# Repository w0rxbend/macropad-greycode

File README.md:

# greycode

A 3 x 3 macropad with a knob and an OLED that changes with the app in front.
FreeCAD in focus: the keys become views, undo and visibility, the OLED shows their names, the edge
light turns orange. A build fails: the edge blinks red and says why.

Keymaps are edited live in [Vial](https://get.vial.today). App profiles, labels, colours and
host actions live in one TOML file that the PC daemon `greyd` reloads on save.

*A render of the case model, not a photo.*

> **Status: design files and software only. Nothing has been built.**
> No board ordered, no case milled, no firmware flashed. Every claim below is what the design files
> and their automatic checks say.

## Status

Checked on 2026-11-15 by running the commands in the last column.

| Part | State | Check |
|---|---|---|
| Firmware | QMK/Vial for RP2040; builds `firmware/dist/greycode_vial.uf2` (vial-qmk `dd43959a`) | `just firmware` |
| Host link (pad side) | 10 native tests pass under ASan + UBSan | `just test-firmware` |
| greyd, greyctl | 45 tests pass, clippy and rustfmt clean. sway backend ran live; Hyprland against fake sockets only; X11 read once on XWayland | `just test-host` |
| FreeCAD add-on | 11 tests against a fake greyd. Not run inside FreeCAD | `just test-freecad` |
| Configurator | Core 32 tests, UI logic 9 tests pass. **Window not built**: needs `webkit2gtk-4.1` | `just test-configurator` |
| PCB | Generated KiCad 9 board, 4 layers, 66 x 96 mm. 892 tracks, 213 vias, 0 unrouted pads. DRC 0 violations, 0 unconnected, 0 parity issues; ERC clean; 8 `board.toml` contract groups match; rebuild byte-repeatable; 48 generator tests | `just pcb`, `just pcb-test` |
| Order files | JLCPCB Gerbers, drill, BOM (22 lines, LCSC numbers), CPL (78 parts); agree with the board. Bottom-side rotations not verified | `just pcb-fab` |
| Case | build123d model, 6061-T6. Self-test 20 of 20; 990 part pairs at rest and 429 pressed, 0 clashes; walls and metal between cuts at least 1.0 mm; inside corners R1.5 wherever the tool reaches over 3 mm; STEP and STL read back clean | `just cad` |
| Pins | 12 checks: firmware and greyd agree with `board.toml` | `just check` |
| Real hardware | **None** | - |

## What it is

| | |
|---|---|
| MCU | RP2040, USB-C |
| Keys | 9 x MX on hot-swap sockets, one GPIO each |
| Knob | EC11 with push. Tap: mute. Hold: FN layer |
| Display | 1.3" 128 x 64 OLED (SH1106, I2C): profile name, the nine key labels, alert text |
| Light | 9 per-key RGB, 6 edge LEDs behind a slot in the case for alerts and the profile colour |
| Firmware | QMK + Vial: 16 layers, encoder map, macros, tap dance, combos, VialRGB |
| Host | `greyd` (Linux: sway, Hyprland, X11), `greyctl`, FreeCAD add-on, configurator |
| Case | Milled 6061-T6 top shell with built-in switch plate and base, knurled knob, frosted light strip in a shadow gap, smoked lens. 77 x 107 x 17.6 mm, 35.0 mm to the knob top. Seven M2 x 10 screws from below |
| PCB | RP2040, W25Q128JVS, USB-C on the underside, 9 hot-swap sockets, 15 SK6812 (9 per key, 6 side-emitting at the front edge), 4 layers |

## Stock keymap

Layer 0 is the base; layers 1-14 are app profiles; 15 is FN (hold the knob).
Edit any of it in Vial; `KC_TRNS` in a profile falls through to the base layer.

| Layer | Keys, row by row | Knob |
|---|---|---|
| 0 Base | Prev Play Next / Copy Paste Undo / HOST0 HOST1 HOST2 | Volume |
| 1 FreeCAD | Iso Front Right / Top Hide Delete / Undo Redo Esc | Zoom |
| 2 KiCad PCB | Route Drag Move / Rotate Via Props / Fill Delete Esc | Zoom (F1/F2) |
| 3 Browser | Reopen New Close / Back URL Forward / Zoom- Zoom0 Zoom+ | Tabs |
| 4 Sketcher | Line Circle Rect / Coincident Horizontal Vertical / Dimension Construction Esc | Zoom |
| 15 FN | RGB on/off, next effect, hue / sat, speed, brightness / -, -, **bootloader** | Brightness |

## Use it

1. **Flash.** Hold BOOT, plug in (or double-tap reset), copy `firmware/dist/greycode_vial.uf2` to the
   `RPI-RP2` drive.
2. **Install greyd** and the udev rule: [host/README.md](host/README.md).
3. **Profiles.** Copy `host/config.example.toml` to `~/.config/greycode/config.toml` and edit it.
4. **Keys.** Open Vial, change a profile's layer. It applies at once.
5. **Alerts.** `greyctl alert error "CI failed" --timeout 60`.
6. **FreeCAD states.** Install the add-on ([freecad/README.md](freecad/README.md)): opening a sketch
   switches the pad to the Sketcher layer.

Before ordering anything, read the open points in [pcb/README.md](pcb/README.md) and
[cad/README.md](cad/README.md), and [docs/architecture.md](docs/architecture.md#open-points).

## Work on it

| Command | Does | Needs |
|---|---|---|
| `just test` | Firmware link, greyd, configurator, FreeCAD add-on, PCB generator, pins (under a minute) | gcc, Rust, Python 3.11+, node |
| `just cad` | Case checks, STEP/STL, renders (about 1 minute) | `cad/.venv` (see `cad/README.md`) |
| `just pcb` | Schematic, placement, routing, DRC, contract, order files | Docker, `kicad/kicad:9.0.9` |
| `just firmware` | Fetch pinned vial-qmk (first run), build the UF2 in the QMK container | Docker |
| `just host-run` | greyd from source with the example config | Rust, sway |

`board.toml` holds pins and parts. Change a pin there, then in `firmware/greycode/`, then run
`just check`.

## Where things are

| Path | What |
|---|---|
| [`board.toml`](board.toml) | Pins and parts; the source the firmware (and later PCB and case) is checked against |
| `firmware/greycode/` | QMK keyboard: `keyboard.json`, `greycode.c` (glue), `hostlink.c` (protocol, no QMK), `keymaps/vial/` |
| `firmware/test/` | Native tests and the protocol vectors shared with greyd |
| [`pcb/`](pcb/README.md) | Board generator (`gen/`), generated KiCad project, JLCPCB files in `fab/` |
| [`cad/`](cad/README.md) | Case model, checks, STEP/STL in `exports/`, machine-shop notes |
| [`configurator/`](configurator/README.md) | Tauri app: `core` (logic), `ui` (HTML/JS), `src-tauri` (shell) |
| [`freecad/`](freecad/README.md) | FreeCAD add-on that reports workbench and Sketcher state to greyd |
| [`host/`](host/README.md) | `greyd` and `greyctl` (Rust), example config, udev rule, systemd unit |
| [`docs/architecture.md`](docs/architecture.md) | How it fits together, failure behaviour, roadmap |
| [`docs/protocol.md`](docs/protocol.md) | Host link wire format |
| `docs/legacy/` | Photos of the hand-wired Pro Micro prototype this replaces |
| `tools/check_pins.py` | Firmware and greyd against `board.toml` |

## License

No license file yet. Until one is added, nobody else has the right to reuse this.

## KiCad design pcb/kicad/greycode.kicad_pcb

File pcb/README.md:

# PCB

The board is generated. Nothing in `pcb/kicad/` is drawn by hand: `make -C pcb place` writes the
schematic, the placed and routed board and the pictures in `docs/images/pcb/` from two inputs,
`board.toml` (outline, holes, positions, GPIOs) and `pcb/gen/circuit.py` (parts and nets). The
generator is adapted from `~/Projects/macropad/pcb`.

**Not built.** No board has been ordered, assembled or powered. Everything below is what the design
files say and what the automatic checks confirm, nothing more.

The part models are block models (`gen/models.py`) with heights typed from memory. They show where
things are and on which face; they are not for measuring.

## Status

Checked on 2026-11-15 with the commands below, KiCad 9.0.9 in Docker.

| Check | Result | Command |
|---|---|---|
| Placement, routing | 96 footprints, 55 nets; 892 tracks, 213 vias, 1330.1 mm; **0 unrouted pads** | `make -C pcb place` |
| Schematic ERC (all severities) | 0 errors, 0 warnings | `make -C pcb place` |
| Schematic netlist vs `circuit.py` | 272 pins match | `make -C pcb place` |
| DRC with schematic parity | 0 violations, 0 unconnected pads, 0 footprint errors | `make -C pcb check` |
| DRC at all severities | only the two accepted findings (J1, J2 differ from their library copy: silkscreen trimmed) | `make -C pcb place` |
| Board vs `board.toml` | 8 groups match: outline, 7 holes with keep-outs, 9 keys, knob, OLED header (pins in `OLED_PINS` order), USB-C (mouth 0.50 mm over), 15 LEDs, 15 GPIOs on their pins and 15 open with no copper | `make -C pcb check` |
| Rebuild repeatable | two `place` runs write byte-identical boards, sha256 `17e881e9...29e0` | `make -C pcb repeat` |
| Order files | 78 machine-placed parts on 22 BOM lines; Gerbers, drill files, BOM and CPL agree with the board | `make -C pcb fab` |
| Plain tests | 48 pass (router 15, schematic writer 19, circuit vs `board.toml` and firmware 11, order files 3) | `make -C pcb test` |
| Real hardware | **None** | - |

## Commands

| Command | Does | Time |
|---|---|---|
| `make -C pcb place` | Schematic, ERC, netlist compare, placement checks, routing, pours, DRC, length checks, contract, pictures. Fails on an unrouted pad after writing `routing.txt`. | about 4 min |
| `make -C pcb check` | `kicad-cli pcb drc --schematic-parity`, fails on any error or unconnected item; then the `board.toml` contract | 30 s |
| `make -C pcb fab` | Gerbers, drill files, `greycode-gerbers.zip`, JLCPCB BOM and CPL into `pcb/fab/`, then a check that they agree with the board | 30 s |
| `make -C pcb test` | Plain Python, no Docker: netlist self-check and the unit tests | 2 s |
| `make -C pcb repeat` | `place` twice, then `cmp` on the two board files | about 8 min |
| `make -C pcb order` | Search a routing order again after moving parts or pins; rewrites `gen/route_order.txt` | about 12 min |

KiCad runs in the pinned container `kicad/kicad:9.0.9` through `pcb/kicad.sh`.

## Circuit

[Schematic PDF](../docs/images/pcb/schematic.pdf), [SVG](../docs/images/pcb/schematic.svg). One A3 sheet,
drawn from `circuit.py` with KiCad's own symbols (RP2040, W25Q128JVS, AP2112K-3.3, USBLC6-2SC6,
SN74LVC1T45DBV, USB-C 16P, EC11). `schematic.check_mcu_pins` holds every RP2040 pin in `circuit.py`
against KiCad's RP2040 symbol.

| Block | Parts |
|---|---|
| MCU | RP2040 (QFN-56, bottom face), W25Q128JVSIQ on QSPI, ABM8-272-T3 12 MHz with 15 pF and 1 k, per "Hardware design with RP2040" |
| MCU supply | 100 nF on each IOVDD, DVDD, USB_VDD and ADC_AVDD pin; 1 uF on VREG_VIN and VREG_VOUT (internal 1.1 V regulator); TESTEN to GND |
| USB | HRO TYPE-C-31-M-12 (bottom face, centred on `usb_x`), 5.1 k on CC1/CC2, USBLC6-2SC6, 27 ohm on D+/D-, nSMD050 500 mA polyfuse, AP2112K-3.3 |
| Buttons | BOOT: QSPI_SS to GND through 1 k. RESET: RUN to GND (RUN's internal pull-up, no external one). Both TS-1187A on the bottom face |
| Keys | 9 MX hot-swap sockets on the bottom face, each between its GPIO and GND, no diodes. Footprint drawn from Kailh CPG151101S11; the BOM orders HanElectricity CPG151101S11-2 (C49352235), see open points |
| Knob | EC11E18244AU at `pcb.knob`: A, B, push to GPIO 12/13/11, C and S2 to GND (internal pull-ups) |
| OLED | 1x4 header GND, VCC (3.3 V), SCL, SDA on GPIO 15/14 (I2C1), 4.7 k pull-ups |
| LEDs | 74LVC1T45 (A at 3.3 V, B at 5 V, DIR high) then 330 ohm, then one chain: 9 x SK6812MINI-E reverse-mounted under the keys, then 6 x SK6812 SIDE-A on the front edge, 100 nF each. Chain order = `keyboard.json` order (checked) |
| Probe pads | SWCLK, SWDIO, GND, 5V, 3V3, 1V1 on the bottom face |

## Board

66 x 96 mm, r 1.5, 1.6 mm, 4 layers, seven M2 holes with 5 mm keep-outs on every copper layer
(rule areas), all from `board.toml`. Every machine-placed part is on the bottom face, so JLCPCB
assembles one side. The encoder and the OLED header are through-hole on the top face, hand-soldered.

| Layer | Use |
|---|---|
| F.Cu | Signals that cross others, ground pour |
| In1.Cu | 5 V plane; 3.3 V island over the strip behind the keys; 1.1 V island under the MCU with a lobe to its capacitors |
| In2.Cu | Ground plane, unbroken |
| B.Cu | All machine-placed parts, most tracks, ground pour |

Drawings: [top](../docs/images/pcb/copper-top.svg), [power](../docs/images/pcb/copper-power.svg),
[ground](../docs/images/pcb/copper-ground.svg), [bottom](../docs/images/pcb/copper-bottom.svg),
assembly [top](../docs/images/pcb/assembly-top.svg), [bottom, mirrored](../docs/images/pcb/assembly-bottom.svg).

Design rules (`layout.py`, written into `kicad/greycode.kicad_pro`): 0.15 mm track and clearance,
0.6/0.3 mm vias, 0.3 mm copper to edge. These are the sibling board's JLCPCB 4-layer values; check
them against JLCPCB's capability page on the day you order.

Routing: `gen/router.py` is a two-layer grid router (no autorouter program). `gen/route.py` runs it
in order: four ground vias in the exposed pad, every MCU supply pin with its capacitor and hand-placed
vias, crystal and ESD ground vias, SWD/RUN escapes, USB and crystal nets, VBUS, flash, one via to the
plane for every other supply pad, LED links inside a key row, MCU signals one escape at a time, the
rest shortest first. `gen/route_order.txt` (found by `make -C pcb order`) moves I2C_SCL, I2C_SDA and
ENC_B to the front.

Routed lengths (`routing.txt`): USB connector to MCU D+ 23.42 mm, D- 21.32 mm; XIN 6.40, XOUT 8.10,
XTAL_DRIVE 3.75 mm; QSPI 4.86 to 15.73 mm. The 15 mm QSPI limit (`route.QSPI_LENGTH_LIMIT`) holds
for every QSPI net but QSPI_SS (15.73 mm), which `route.check_sensitive_lengths` leaves out because
it runs on past the flash to the BOOT button's 1 k resistor.

## Order files (`pcb/fab/`)

`greycode-gerbers.zip` (11 Gerber layers, PTH and NPTH drill files), `bom-jlcpcb.csv` (Comment,
Designator, Footprint, LCSC Part #, Manufacturer, Manufacturer Part #), `cpl-jlcpcb.csv`
(Designator, Mid X, Mid Y, Layer, Rotation; Y negative as JLCPCB's KiCad flow writes it) and
`board-sha256.txt`, the board they were made from. `make -C pcb test` fails if the board changes
after `make -C pcb fab`.

LCSC numbers: the parts shared with `~/Projects/macropad` were checked there on 2026-11-12. RP2040
(C2040), W25Q128JVSIQ (C97521), SK6812MINI-E (C5149201) and 4.7 k 0402 (C25900) were checked
against their JLCPCB part pages on 2026-11-15: part number and package only, not stock or price.

Hand-soldered, not in the BOM: EC11E18244AU (C202365) and the 1x4 header (C2337 strip, only if the
OLED module comes without pins).

## Open points

Nothing below is verified on hardware.

- **Bottom-side rotations in the CPL.** KiCad's rotation is written unchanged for bottom parts, and
  the placement point is the body centre. JLCPCB sometimes wants a correction on bottom parts. Check
  every part in JLCPCB's placement preview before paying, especially U1, U5, the LEDs and J1.
- **SK6812MINI-E footprint.** Pin functions (1 VDD, 2 DOUT, 3 GND, 4 DIN) agree with the OPSCO and
  Mutipower pin tables. Pad size, pad positions, cut-out size and which corner pin 1 lands on when
  the part is mounted upside down are guesses (MEASURE). Also ask JLCPCB whether they place
  reverse-mount MINI-E parts; not confirmed.
- **Part substitutions against the brief.** (1) The brief names Kailh hot-swap sockets; the BOM
  orders HanElectricity CPG151101S11-2 (LCSC C49352235), the part the sibling board uses. The
  footprint is drawn from Kailh's CPG151101S11 drawing; that the HanElectricity part shares its pad
  pattern is a guess from the part number (MEASURE against its datasheet, or swap in Kailh's LCSC
  number before ordering). (2) The brief does not list R9, a 330 ohm resistor between the level
  shifter and the first LED, added because the SK6812 SIDE-A datasheet asks for one in the data line.
  (3) Parts the brief left to me: USB-C HRO TYPE-C-31-M-12, fuse TECHFUSE nSMD050; LCSC stock not
  checked.
- **SK6812 SIDE-A pin order** comes from the sibling's footprint (MEASURE).
- **OLED header.** Pin order GND VCC SCL SDA and the row 1.6 mm inside the module's back edge are
  guesses (`circuit.OLED_PINS`, `OLED_HEADER_INSET`, MEASURE). Modules with VCC and GND swapped exist.
  The contract holds the board's header pins, left to right, against `circuit.OLED_PINS`. The module
  size 35.4 x 33.5 mm is typed into `circuit.OLED_MODULE_SIZE` from a comment in `board.toml`, and the
  contract reuses that copy, so "header at the module's back" is not an independent check until
  `board.toml` gets a `pcb.oled_module_size` key (requested).
- **USB-C on the bottom face**, mouth 0.5 mm past the back edge (`circuit.USB_MOUTH_OVERHANG`; the
  contract measures the fab outline without its line width and prints the same 0.50 mm). The case
  needs to know both; they are not in `board.toml` yet.
- **Buttons on the bottom face** need holes in the case floor: BOOT at board.toml (42.0, 63.6), RESET
  at (8.0, 87.0).
- **LED current.** 15 LEDs at up to about 60 mA each at full white is about 0.9 A; the polyfuse holds
  500 mA. The firmware's `max_brightness` 160/255 still allows about 0.56 A. Nobody has measured it.
- **1.1 V decoupling.** The DVDD and VREG_VOUT capacitors (C8, C9, C10) sit 7 to 12 mm from their
  pins and reach them through the 1.1 V island on In1, not by a track. IOVDD pin 10's capacitor (C2)
  also connects through the plane. The RP2040 guide wants them close; this is the compromise the
  pin-out allowed.
- **Two length checks were loosened after the first full route**, both numbers picked without a
  datasheet: the USB D+/D- mismatch limit from the sibling's 2.0 mm to 3.0 mm (measured 2.09 mm), and
  the MCU-side stub of each 27 ohm resistor from 6 mm to 8 mm (measured 7.16 and 7.53 mm). Full-speed
  USB does not care at these sizes; the reasons are in `route.py`. No USB impedance was calculated.
- **VBUS capacitance.** 2.2 uF plus 16 x 100 nF on 5 V (about 3.8 uF); the 10 uF on 3.3 V sits behind
  the regulator. Not measured at plug-in.
- **Crystal** uses Raspberry Pi's reference values; the oscillator is not measured.
- **Fiducials** are three 1 mm marks on the bottom face; JLCPCB adds its own tooling holes.
- **No teardrops**, thermal reliefs only on through-hole pads.
- **Schematic** is generated and passes ERC; no engineer has reviewed it as a drawing.

## Files

| Path | What |
|---|---|
| `gen/circuit.py` | Every part, its LCSC and manufacturer number, position, rotation and nets. Pure Python |
| `gen/layout.py` | Footprints, outline, planes, keep-outs, design rules, exposed-pad paste windows, placement checks |
| `gen/router.py`, `gen/route.py`, `gen/route_order.txt` | Grid router, routing plan, routing order |
| `gen/schematic.py`, `gen/sheet_layout.py`, `gen/symlib.py`, `gen/sexpr.py` | Schematic writer |
| `gen/contract.py` | The routed board against `board.toml` |
| `gen/silk.py`, `gen/models.py` | Silkscreen text, block 3D models |
| `gen/fab.py` | JLCPCB BOM and CPL and their checks |
| `gen/build.py` | The steps: `place`, `order`, `contract`, `fab` |
| `gen/test_*.py` | Plain Python tests |
| `kicad/` | Generated KiCad 9 project |
| `lib/` | Project footprints (`lib/SOURCES.txt`) and generated block models |
| `fab/` | Generated order files |
| `routing.txt`, `netlist.txt` | Generated routing report and netlist |

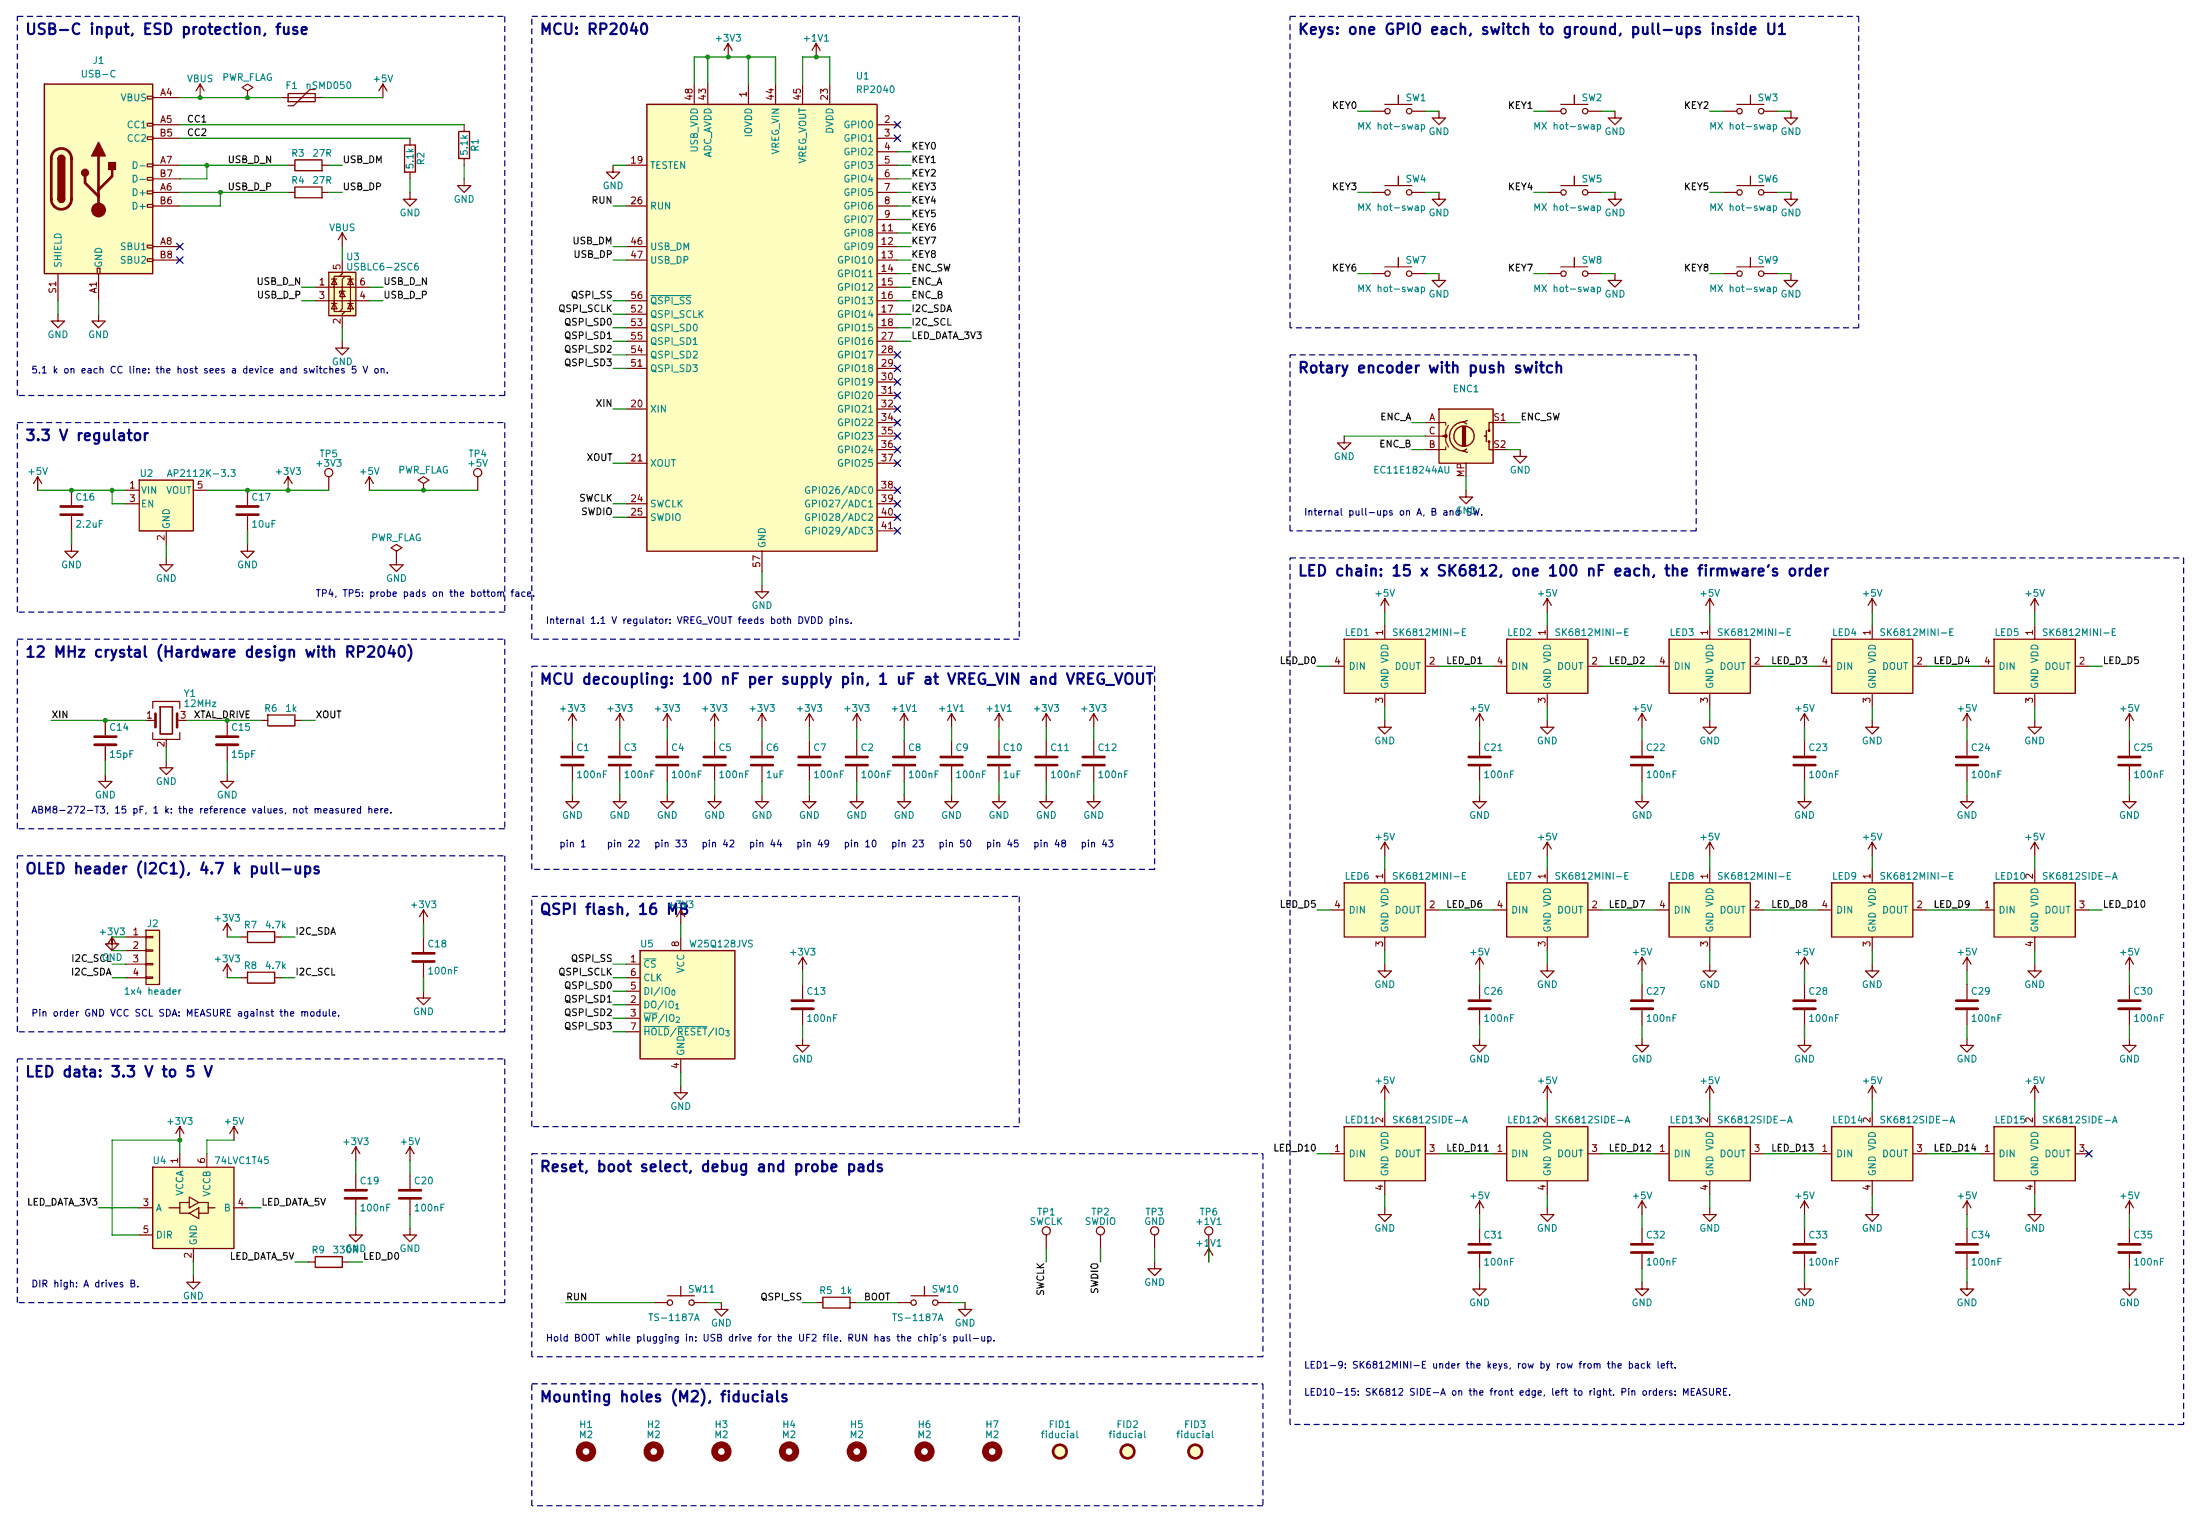
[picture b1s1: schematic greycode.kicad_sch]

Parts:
C1, C2, C3, C4, C5, C7, C8, C9, C11, C12, C13, C18, C19, C20, C21, C22, C23, C24, C25, C26, C27, C28, C29, C30, C31, C32, C33, C34, C35: 100nF; C_0402_1005Metric; LCSC C1525
C6, C10: 1uF; C_0402_1005Metric; LCSC C52923
C14, C15: 15pF; C_0402_1005Metric; LCSC C1548
C16: 2.2uF; C_0603_1608Metric; LCSC C23630
C17: 10uF; C_0603_1608Metric; LCSC C19702
ENC1: EC11E18244AU; RotaryEncoder_Alps_EC11E-Switch_Vertical_H20mm; LCSC C202365
F1: nSMD050; Fuse_1206_3216Metric; LCSC C69688
FID1, FID2, FID3: fiducial; Fiducial_1mm_Mask2mm
H1, H2, H3, H4, H5, H6, H7: M2; Hole_M2
J1: USB-C; USB_C_Receptacle_HRO_TYPE-C-31-M-12; LCSC C165948
J2: 1x4 header; PinHeader_1x04_P2.54mm_Vertical; LCSC C2337
LED1, LED2, LED3, LED4, LED5, LED6, LED7, LED8, LED9: SK6812MINI-E; SK6812MINI-E_Reverse; LCSC C5149201
LED10, LED11, LED12, LED13, LED14, LED15: SK6812SIDE-A; SK6812-side-a; LCSC C5378721
R1, R2: 5.1k; R_0402_1005Metric; LCSC C25905
R3, R4: 27R; R_0402_1005Metric; LCSC C25100
R5, R6: 1k; R_0402_1005Metric; LCSC C11702
R7, R8: 4.7k; R_0402_1005Metric; LCSC C25900
R9: 330R; R_0402_1005Metric; LCSC C25104
SW1, SW2, SW3, SW4, SW5, SW6, SW7, SW8, SW9: MX hot-swap; MX_Hotswap; LCSC C49352235
SW10, SW11: TS-1187A; SW_Push_1P1T_XKB_TS-1187A; LCSC C318884
TP1: SWCLK; TestPoint_Pad_D1.0mm
TP2: SWDIO; TestPoint_Pad_D1.0mm
TP3: GND; TestPoint_Pad_D1.0mm
TP4: +5V; TestPoint_Pad_D1.0mm
TP5: +3V3; TestPoint_Pad_D1.0mm
TP6: +1V1; TestPoint_Pad_D1.0mm
U1: RP2040; QFN-56-1EP_7x7mm_P0.4mm_EP3.2x3.2mm_ViaWindows; LCSC C2040
U2: AP2112K-3.3; SOT-23-5; LCSC C51118
U3: USBLC6-2SC6; SOT-23-6; LCSC C7519
U4: 74LVC1T45; SOT-23-6; LCSC C168856
U5: W25Q128JVS; SOIC-8_5.3x5.3mm_P1.27mm; LCSC C97521
Y1: 12MHz; Crystal_SMD_3225-4Pin_3.2x2.5mm; LCSC C20625731

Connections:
+1V1: C8.1, C9.1, C10.1, TP6.1, U1.23 (DVDD), U1.45 (VREG_VOUT), U1.50 (DVDD)
+3V3: C1.1, C2.1, C3.1, C4.1, C5.1, C6.1, C7.1, C11.1, C12.1, C13.1, C17.1, C18.1, C19.1, J2.2, R7.2, R8.2, TP5.1, U1.1 (IOVDD), U1.10 (IOVDD), U1.22 (IOVDD), U1.33 (IOVDD), U1.42 (IOVDD), U1.43 (ADC_AVDD), U1.44 (VREG_VIN), U1.48 (USB_VDD), U1.49 (IOVDD), U2.5 (VOUT), U4.1 (VCCA), U4.5 (DIR), U5.8 (VCC)
+5V: C16.1, C20.1, C21.1, C22.1, C23.1, C24.1, C25.1, C26.1, C27.1, C28.1, C29.1, C30.1, C31.1, C32.1, C33.1, C34.1, C35.1, F1.2, LED1.1 (VDD), LED2.1 (VDD), LED3.1 (VDD), LED4.1 (VDD), LED5.1 (VDD), LED6.1 (VDD), LED7.1 (VDD), LED8.1 (VDD), LED9.1 (VDD), LED10.2 (VDD), LED11.2 (VDD), LED12.2 (VDD), LED13.2 (VDD), LED14.2 (VDD), LED15.2 (VDD), TP4.1, U2.1 (VIN), U2.3 (EN), U4.6 (VCCB)
/BOOT: R5.2, SW10.1
/CC1: J1.A5 (CC1), R1.1
/CC2: J1.B5 (CC2), R2.1
/ENC_A: ENC1.A, U1.15 (GPIO12)
/ENC_B: ENC1.B, U1.16 (GPIO13)
/ENC_SW: ENC1.S1, U1.14 (GPIO11)
/I2C_SCL: J2.3, R8.1, U1.18 (GPIO15)
/I2C_SDA: J2.4, R7.1, U1.17 (GPIO14)
/KEY0: SW1.1, U1.4 (GPIO2)
/KEY1: SW2.1, U1.5 (GPIO3)
/KEY2: SW3.1, U1.6 (GPIO4)
/KEY3: SW4.1, U1.7 (GPIO5)
/KEY4: SW5.1, U1.8 (GPIO6)
/KEY5: SW6.1, U1.9 (GPIO7)
/KEY6: SW7.1, U1.11 (GPIO8)
/KEY7: SW8.1, U1.12 (GPIO9)
/KEY8: SW9.1, U1.13 (GPIO10)
/LED_D0: LED1.4 (DIN), R9.2
/LED_D1: LED1.2 (DOUT), LED2.4 (DIN)
/LED_D2: LED2.2 (DOUT), LED3.4 (DIN)
/LED_D3: LED3.2 (DOUT), LED4.4 (DIN)
/LED_D4: LED4.2 (DOUT), LED5.4 (DIN)
/LED_D5: LED5.2 (DOUT), LED6.4 (DIN)
/LED_D6: LED6.2 (DOUT), LED7.4 (DIN)
/LED_D7: LED7.2 (DOUT), LED8.4 (DIN)
/LED_D8: LED8.2 (DOUT), LED9.4 (DIN)
/LED_D9: LED9.2 (DOUT), LED10.1 (DIN)
/LED_D10: LED10.3 (DOUT), LED11.1 (DIN)
/LED_D11: LED11.3 (DOUT), LED12.1 (DIN)
/LED_D12: LED12.3 (DOUT), LED13.1 (DIN)
/LED_D13: LED13.3 (DOUT), LED14.1 (DIN)
/LED_D14: LED14.3 (DOUT), LED15.1 (DIN)
/LED_DATA_3V3: U1.27 (GPIO16), U4.3 (A)
/LED_DATA_5V: R9.1, U4.4 (B)
/QSPI_SCLK: U1.52 (QSPI_SCLK), U5.6 (CLK)
/QSPI_SD0: U1.53 (QSPI_SD0), U5.5 (DI/IO_{0})
/QSPI_SD1: U1.55 (QSPI_SD1), U5.2 (DO/IO_{1})
/QSPI_SD2: U1.54 (QSPI_SD2), U5.3 (~WP/IO_{2})
/QSPI_SD3: U1.51 (QSPI_SD3), U5.7 (~HOLD/~RESET/IO_{3})
/QSPI_SS: R5.1, U1.56 (~QSPI_SS), U5.1 (~CS)
/RUN: SW11.1, U1.26 (RUN)
/SWCLK: TP1.1, U1.24 (SWCLK)
/SWDIO: TP2.1, U1.25 (SWDIO)
/USB_DM: R3.2, U1.46 (USB_DM)
/USB_DP: R4.2, U1.47 (USB_DP)
/USB_D_N: J1.A7 (D-), J1.B7 (D-), R3.1, U3.1 (I/O1), U3.6 (I/O1)
/USB_D_P: J1.A6 (D+), J1.B6 (D+), R4.1, U3.3 (I/O2), U3.4 (I/O2)
/XIN: C14.1, U1.20 (XIN), Y1.1
/XOUT: R6.1, U1.21 (XOUT)
/XTAL_DRIVE: C15.1, R6.2, Y1.3
GND: C1.2, C2.2, C3.2, C4.2, C5.2, C6.2, C7.2, C8.2, C9.2, C10.2, C11.2, C12.2, C13.2, C14.2, C15.2, C16.2, C17.2, C18.2, C19.2, C20.2, C21.2, C22.2, C23.2, C24.2, C25.2, C26.2, C27.2, C28.2, C29.2, C30.2, C31.2, C32.2, C33.2, C34.2, C35.2, ENC1.C, ENC1.MP, ENC1.S2, J1.A1 (GND), J1.A12 (GND), J1.B1 (GND), J1.B12 (GND), J1.S1 (SHIELD), J2.1, LED1.3 (GND), LED2.3 (GND), LED3.3 (GND), LED4.3 (GND), LED5.3 (GND), LED6.3 (GND), LED7.3 (GND), LED8.3 (GND), LED9.3 (GND), LED10.4 (GND), LED11.4 (GND), LED12.4 (GND), LED13.4 (GND), LED14.4 (GND), LED15.4 (GND), R1.2, R2.2, SW1.2, SW2.2, SW3.2, SW4.2, SW5.2, SW6.2, SW7.2, SW8.2, SW9.2, SW10.2, SW11.2, TP3.1, U1.19 (TESTEN), U1.57 (GND), U2.2 (GND), U3.2 (GND), U4.2 (GND), U5.4 (GND), Y1.2 (G), Y1.4 (G)
VBUS: F1.1, J1.A4 (VBUS), J1.A9 (VBUS), J1.B4 (VBUS), J1.B9 (VBUS), U3.5 (VBUS)

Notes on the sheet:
USB-C input, ESD protection, fuse
5.1 k on each CC line: the host sees a device and switches 5 V on.
3.3 V regulator
TP4, TP5: probe pads on the bottom face.
12 MHz crystal (Hardware design with RP2040)
ABM8-272-T3, 15 pF, 1 k: the reference values, not measured here.
OLED header (I2C1), 4.7 k pull-ups
Pin order GND VCC SCL SDA: MEASURE against the module.
LED data: 3.3 V to 5 V
DIR high: A drives B.
MCU: RP2040
Internal 1.1 V regulator: VREG_VOUT feeds both DVDD pins.
MCU decoupling: 100 nF per supply pin, 1 uF at VREG_VIN and VREG_VOUT
pin 1
pin 22
pin 33
pin 42
pin 44
pin 49
pin 10
pin 23
pin 50
pin 45
pin 48
pin 43
QSPI flash, 16 MB
Reset, boot select, debug and probe pads
Hold BOOT while plugging in: USB drive for the UF2 file. RUN has the chip's pull-up.
Mounting holes (M2), fiducials
Keys: one GPIO each, switch to ground, pull-ups inside U1
Rotary encoder with push switch
Internal pull-ups on A, B and SW.
LED chain: 15 x SK6812, one 100 nF each, the firmware's order
LED1-9: SK6812MINI-E under the keys, row by row from the back left.
LED10-15: SK6812 SIDE-A on the front edge, left to right. Pin orders: MEASURE.

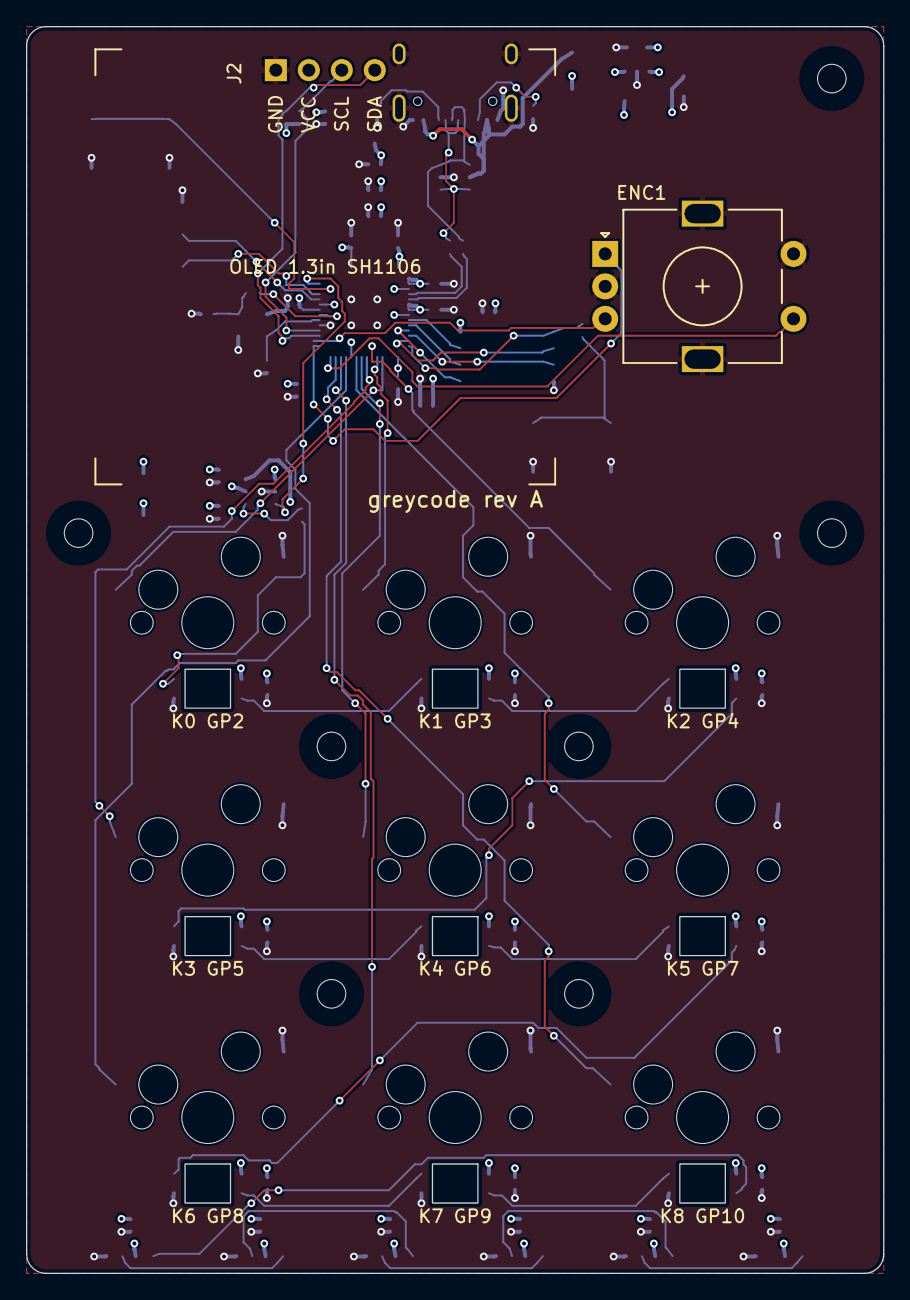
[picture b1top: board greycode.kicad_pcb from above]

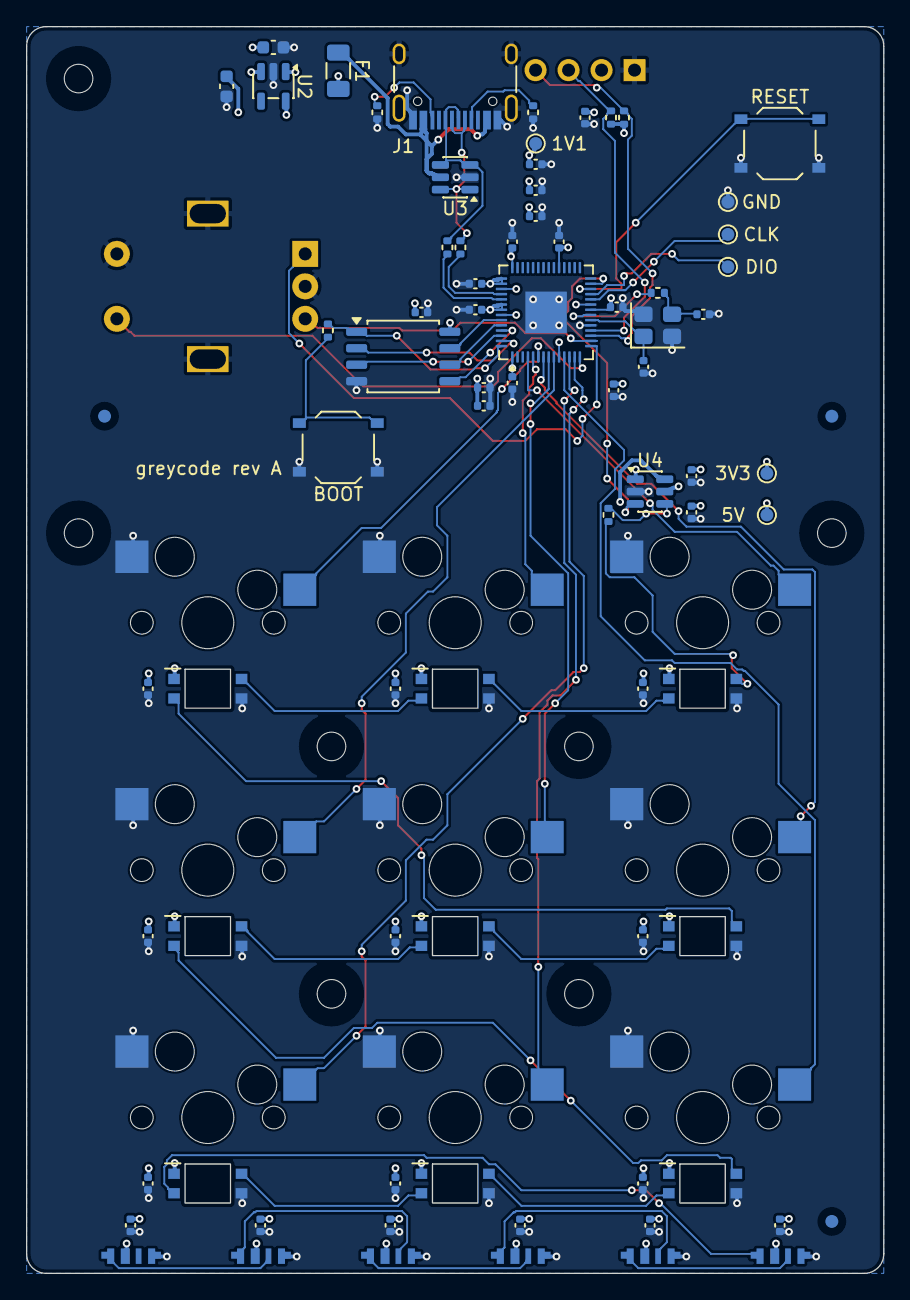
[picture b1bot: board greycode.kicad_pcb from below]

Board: 4 copper layers, 66.0 x 96.0 mm, 96 parts (87 on the bottom side), 55 nets.

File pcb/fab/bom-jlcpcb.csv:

Comment,Designator,Footprint,LCSC Part #,Manufacturer,Manufacturer Part #
100nF,"C1,C3,C4,C5,C7,C2,C8,C9,C11,C12,C13,C18,C19,C20,C21,C22,C23,C24,C25,C26,C27,C28,C29,C30,C31,C32,C33,C34,C35",C_0402_1005Metric,C1525,Samsung Electro-Mechanics,CL05B104KO5NNNC
10uF,C17,C_0603_1608Metric,C19702,Samsung Electro-Mechanics,CL10A106KP8NNNC
12MHz,Y1,Crystal_SMD_3225-4Pin_3.2x2.5mm,C20625731,Abracon,ABM8-272-T3
15pF,"C14,C15",C_0402_1005Metric,C1548,FH (Guangdong Fenghua),0402CG150J500NT
1k,"R6,R5",R_0402_1005Metric,C11702,UNI-ROYAL,0402WGF1001TCE
1uF,"C6,C10",C_0402_1005Metric,C52923,Samsung Electro-Mechanics,CL05A105KA5NQNC
2.2uF,C16,C_0603_1608Metric,C23630,Samsung Electro-Mechanics,CL10A225KO8NNNC
27R,"R3,R4",R_0402_1005Metric,C25100,UNI-ROYAL,0402WGF270JTCE
330R,R9,R_0402_1005Metric,C25104,UNI-ROYAL,0402WGF3300TCE
4.7k,"R7,R8",R_0402_1005Metric,C25900,UNI-ROYAL,0402WGF4701TCE
5.1k,"R1,R2",R_0402_1005Metric,C25905,UNI-ROYAL,0402WGF5101TCE
74LVC1T45,U4,SOT-23-6,C168856,Diodes Incorporated,74LVC1T45W6-7
AP2112K-3.3,U2,SOT-23-5,C51118,Diodes Incorporated,AP2112K-3.3TRG1
MX hot-swap,"SW1,SW2,SW3,SW4,SW5,SW6,SW7,SW8,SW9",MX_Hotswap,C49352235,HanElectricity,CPG151101S11-2
RP2040,U1,QFN-56-1EP_7x7mm_P0.4mm_EP3.2x3.2mm_ViaWindows,C2040,Raspberry Pi,RP2040
SK6812MINI-E,"LED1,LED2,LED3,LED4,LED5,LED6,LED7,LED8,LED9",SK6812MINI-E_Reverse,C5149201,OPSCO Optoelectronics,SK6812MINI-E
SK6812SIDE-A,"LED10,LED11,LED12,LED13,LED14,LED15",SK6812-side-a,C5378721,OPSCO Optoelectronics,SK6812SIDE-A
TS-1187A,"SW11,SW10",SW_Push_1P1T_XKB_TS-1187A,C318884,XKB Connection,TS-1187A-B-A-B
USB-C,J1,USB_C_Receptacle_HRO_TYPE-C-31-M-12,C165948,HRO (Korean Hroparts Elec),TYPE-C-31-M-12
USBLC6-2SC6,U3,SOT-23-6,C7519,STMicroelectronics,USBLC6-2SC6
W25Q128JVS,U5,SOIC-8_5.3x5.3mm_P1.27mm,C97521,Winbond,W25Q128JVSIQ
nSMD050,F1,Fuse_1206_3216Metric,C69688,TECHFUSE,nSMD050

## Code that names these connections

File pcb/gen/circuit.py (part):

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    spec = BOARD_SPEC
    nets = {gpio: key_net(i) for i, gpio in enumerate(spec["keys"]["gpio"])}
    knob = spec["knob"]
    nets[knob["gpio_a"]] = "ENC_A"
    nets[knob["gpio_b"]] = "ENC_B"
    nets[knob["gpio_push"]] = "ENC_SW"
    display = spec["display"]
    nets[display["gpio_sda"]] = "I2C_SDA"
    nets[display["gpio_scl"]] = "I2C_SCL"
    nets[spec["leds"]["gpio_data"]] = "LED_DATA_3V3"
    return nets


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
def _clock_and_reset() -> list[Part]:
    return [
        # 12 MHz crystal in front of XIN and XOUT (pins 20 and 21), the reference part and values of
        # "Hardware design with RP2040": ABM8-272-T3, 15 pF load capacitors, 1 k in series from XOUT.
        Part("Y1", "12MHz", "XTAL3225", 17.4, 23.0, 0,
             nets={"1": "XIN", "2": GND, "3": "XTAL_DRIVE", "4": GND}),
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
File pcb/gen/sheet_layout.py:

"""Where everything sits on the schematic sheet. Data only; schematic.py draws it.

Units are grid steps of 1.27 mm. Inside a block, positions count from the block's top-left corner,
X to the right and Y down. A point is either a pin ("R7.1") or a position (x, y).

What is not listed here is drawn by rule (see schematic.py): a pin on a supply net gets a short
wire and the supply symbol, a pin on a signal net gets a short wire and the net's label, an open
pin gets a no-connect mark.
"""

from __future__ import annotations

from dataclasses import dataclass

import circuit
from circuit import GND, V1, V3, V5, VBUS


@dataclass(frozen=True)
class Place:
    ref: str
    x: int
    y: int
    rotation: int = 0  # degrees counter-clockwise


@dataclass(frozen=True)
class Wire:
    """A chain of straight wires through the points. Every pin on it must be on this net in circuit.py."""
    net: str
    points: tuple
    label: tuple | None = None  # (x, y) on the wire, text to the right; (x, y, "left") for text to the left


@dataclass(frozen=True)
class Rail:
    """A supply symbol at this point."""
    net: str
    point: tuple[int, int]


@dataclass(frozen=True)
class Flag:
    """KiCad's PWR_FLAG: tells the rule check that this net is driven from outside the sheet's symbols
    (through the fuse, an inductor or a resistor)."""
    point: tuple[int, int]


@dataclass(frozen=True)
class Note:
    text: str
    x: int
    y: int


@dataclass(frozen=True)
class Block:
    title: str
    x: int
    y: int
    width: int
    height: int
    places: tuple[Place, ...]
    wires: tuple[Wire, ...] = ()
    rails: tuple[Rail, ...] = ()
    flags: tuple[Flag, ...] = ()
    notes: tuple[Note, ...] = ()


PAPER = "A3"
SHEET_WIDTH, SHEET_HEIGHT = 330, 233  # A3 landscape in grid steps

_USB = Block(
    "USB-C input, ESD protection, fuse", 6, 10, 72, 56,
    places=(Place("J1", 12, 24), Place("F1", 42, 12, 90), Place("R2", 58, 21), Place("R1", 66, 19),
            Place("R3", 43, 22, 90), Place("R4", 43, 26, 90), Place("U3", 48, 40)),
    wires=(
        Wire(VBUS, ("J1.A4", (27, 12), (34, 12), "F1.1")),
        Wire(V5, ("F1.2", (54, 12))),
        Wire("CC1", ("J1.A5", "R1.1"), label=(25, 16)),
        Wire("CC2", ("J1.B5", "R2.1"), label=(25, 18)),
        Wire("USB_D_N", ("J1.A7", (28, 22), "R3.1"), label=(31, 22)),
        Wire("USB_D_N", ("J1.B7", (28, 24), (28, 22))),
        Wire("USB_D_P", ("J1.A6", (30, 26), "R4.1"), label=(31, 26)),
        Wire("USB_D_P", ("J1.B6", (30, 28), (30, 26))),
    ),
    rails=(Rail(VBUS, (27, 12)), Rail(V5, (54, 12))),
    flags=(Flag((34, 12)),),
    notes=(Note("5.1 k on each CC line: the host sees a device and switches 5 V on.", 2, 53),),
)

_REGULATOR_3V3 = Block(
    "3.3 V regulator", 6, 70, 72, 28,
    places=(Place("U2", 22, 12), Place("C16", 8, 13), Place("C17", 34, 13), Place("TP5", 46, 10),
            Place("TP4", 68, 10)),
    wires=(
        Wire(V5, ((3, 10), "C16.1", (14, 10), "U2.1")),
        Wire(V5, ("U2.3", (14, 12), (14, 10))),
        Wire(V3, ("U2.5", "C17.1", (40, 10), "TP5.1")),
        Wire(V5, ((52, 10), (60, 10), "TP4.1")),
    ),
    rails=(Rail(V5, (3, 10)), Rail(V3, (40, 10)), Rail(V5, (52, 10)), Rail(GND, (56, 20))),
    flags=(Flag((60, 10)), Flag((56, 20))),
    notes=(Note("TP4, TP5: probe pads on the bottom face.", 44, 26),),
)

_CLOCK = Block(
    "12 MHz crystal (Hardware design with RP2040)", 6, 102, 72, 28,
    places=(Place("Y1", 22, 12), Place("C14", 13, 15), Place("C15", 31, 15), Place("R6", 39, 12, 270)),
    wires=(
        Wire("XIN", ((5, 12), "C14.1", "Y1.1"), label=(5, 12)),
        Wire("XTAL_DRIVE", ("Y1.3", "C15.1", "R6.2"), label=(26, 12)),
    ),
    notes=(Note("ABM8-272-T3, 15 pF, 1 k: the reference values, not measured here.", 2, 26),),
)

_DISPLAY = Block(
    "OLED header (I2C1), 4.7 k pull-ups", 6, 134, 72, 26,
    places=(Place("J2", 20, 14), Place("R7", 36, 12, 270), Place("R8", 36, 18, 270), Place("C18", 60, 15)),
    notes=(Note("Pin order GND VCC SCL SDA: MEASURE against the module.", 2, 24),),
)

_LEVEL_SHIFTER = Block(
    "LED data: 3.3 V to 5 V", 6, 164, 72, 36,
    places=(Place("U4", 26, 22), Place("C19", 50, 20), Place("C20", 58, 20), Place("R9", 46, 30, 90)),
    wires=(
        Wire(V3, ("U4.1", (24, 12), (14, 12), (14, 26), "U4.5")),
        Wire(V5, ("U4.6", (28, 12), (32, 12))),
        Wire("LED_DATA_3V3", ("U4.3", (12, 22)), label=(12, 22, "left")),
    ),
    rails=(Rail(V3, (24, 12)), Rail(V5, (32, 12))),
    notes=(Note("DIR high: A drives B.", 2, 34),),
)

_MCU_X, _MCU_Y = 34, 46
_MCU = Block(
    "MCU: RP2040", 82, 10, 72, 92,
    places=(Place("U1", _MCU_X, _MCU_Y),),
    wires=(
        Wire(V3, ("U1.48", (24, 6), (26, 6), (29, 6), (32, 6), (36, 6), "U1.44")),
        Wire(V3, ("U1.43", (26, 6))),
        Wire(V3, ("U1.1", (32, 6))),
        Wire(V1, ("U1.45", (40, 6), (42, 6), (44, 6), "U1.23")),
    ),
    rails=(Rail(V3, (29, 6)), Rail(V1, (42, 6))),
    notes=(Note("Internal 1.1 V regulator: VREG_VOUT feeds both DVDD pins.", 2, 90),),
)

_DECOUPLING_PITCH = 7
_DECOUPLING_PINS = circuit.DECOUPLING_CAPS | circuit.SECOND_SUPPLY_CAPS
_DECOUPLING = Block(
    "MCU decoupling: 100 nF per supply pin, 1 uF at VREG_VIN and VREG_VOUT", 82, 106, 92, 30,
    places=tuple(Place(ref, 6 + _DECOUPLING_PITCH * n, 14) for n, ref in enumerate(_DECOUPLING_PINS)),
    notes=tuple(Note(f"pin {pin}", 4 + _DECOUPLING_PITCH * n, 27) for n, pin in enumerate(_DECOUPLING_PINS.values())),
)

_FLASH = Block(
    "QSPI flash, 16 MB", 82, 140, 72, 34,
    places=(Place("U5", 22, 16), Place("C13", 40, 16)),
)

_RESET_BOOT_DEBUG = Block(
    "Reset, boot select, debug and probe pads", 82, 178, 108, 30,
    places=(Place("SW11", 22, 22), Place("R5", 45, 22, 90), Place("SW10", 58, 22),
            Place("TP1", 76, 14), Place("TP2", 84, 14), Place("TP3", 92, 14), Place("TP6", 100, 14)),
    wires=(
        Wire("RUN", ((5, 22), "SW11.1"), label=(5, 22)),
        Wire("BOOT", ("R5.2", "SW10.1"), label=(49, 22)),
    ),
    notes=(Note("Hold BOOT while plugging in: USB drive for the UF2 file. RUN has the chip's pull-up.", 2, 28),),
)

_MECHANICAL_REFS = [f"H{n}" for n in range(1, len(circuit.PCB["holes"]) + 1)] + [f"FID{n}" for n in range(1, 4)]
_MECHANICAL = Block(
    "Mounting holes (M2), fiducials", 82, 212, 108, 18,
    places=tuple(Place(ref, 8 + 10 * n, 10) for n, ref in enumerate(_MECHANICAL_REFS)),
)

_KEY_COLUMNS = len(circuit.PCB["key_x"])
_KEYS = Block(
    "Keys: one GPIO each, switch to ground, pull-ups inside U1", 194, 10, 84, 46,
    places=tuple(Place(f"SW{i + 1}", 16 + 26 * (i % _KEY_COLUMNS), 14 + 12 * (i // _KEY_COLUMNS))
                 for i in range(circuit.KEY_COUNT)),
)

_ENCODER = Block(
    "Rotary encoder with push switch", 194, 60, 60, 26,
    places=(Place("ENC1", 26, 12),),
    wires=(Wire(GND, ("ENC1.C", (8, 12))),),
    rails=(Rail(GND, (8, 12)),),
    notes=(Note("Internal pull-ups on A, B and SW.", 2, 24),),
)

_LED_PITCH = 24
_LEDS_PER_ROW = 5
_LED_ROW_PITCH = 36


def _leds() -> Block:
    """The LED chain in rows of five, each LED with its 100 nF below and to the right."""
    count = circuit.KEY_COUNT + len(circuit.BOARD_SPEC["leds"]["edge_x"])
    places, wires = [], []
    for i in range(count):
        row, column = divmod(i, _LEDS_PER_ROW)
        x, y = 14 + _LED_PITCH * column, 16 + _LED_ROW_PITCH * row
        places.append(Place(f"LED{i + 1}", x, y))
        places.append(Place(f"C{21 + i}", x + 14, y + 14))
        if column < _LEDS_PER_ROW - 1 and i < count - 1:
            wires.append(Wire(f"LED_D{i + 1}", (f"LED{i + 1}.{_DOUT[i < circuit.KEY_COUNT]}",
                                                 f"LED{i + 2}.{_DIN[i + 1 < circuit.KEY_COUNT]}"), label=(x + 9, y)))
    notes = (Note("LED1-9: SK6812MINI-E under the keys, row by row from the back left.", 2, 120),
             Note("LED10-15: SK6812 SIDE-A on the front edge, left to right. Pin orders: MEASURE.", 2, 124))
    return Block("LED chain: 15 x SK6812, one 100 nF each, the firmware's order", 194, 90, 132, 128,
                 tuple(places), tuple(wires), notes=notes)


# Data pins per LED type: MINI-E (True) and SIDE-A (False). See circuit._leds.
_DOUT = {True: "2", False: "3"}
_DIN = {True: "4", False: "1"}

BLOCKS = (_USB, _REGULATOR_3V3, _CLOCK, _DISPLAY, _LEVEL_SHIFTER, _MCU, _DECOUPLING, _FLASH, _RESET_BOOT_DEBUG,
          _MECHANICAL, _KEYS, _ENCODER, _leds())
